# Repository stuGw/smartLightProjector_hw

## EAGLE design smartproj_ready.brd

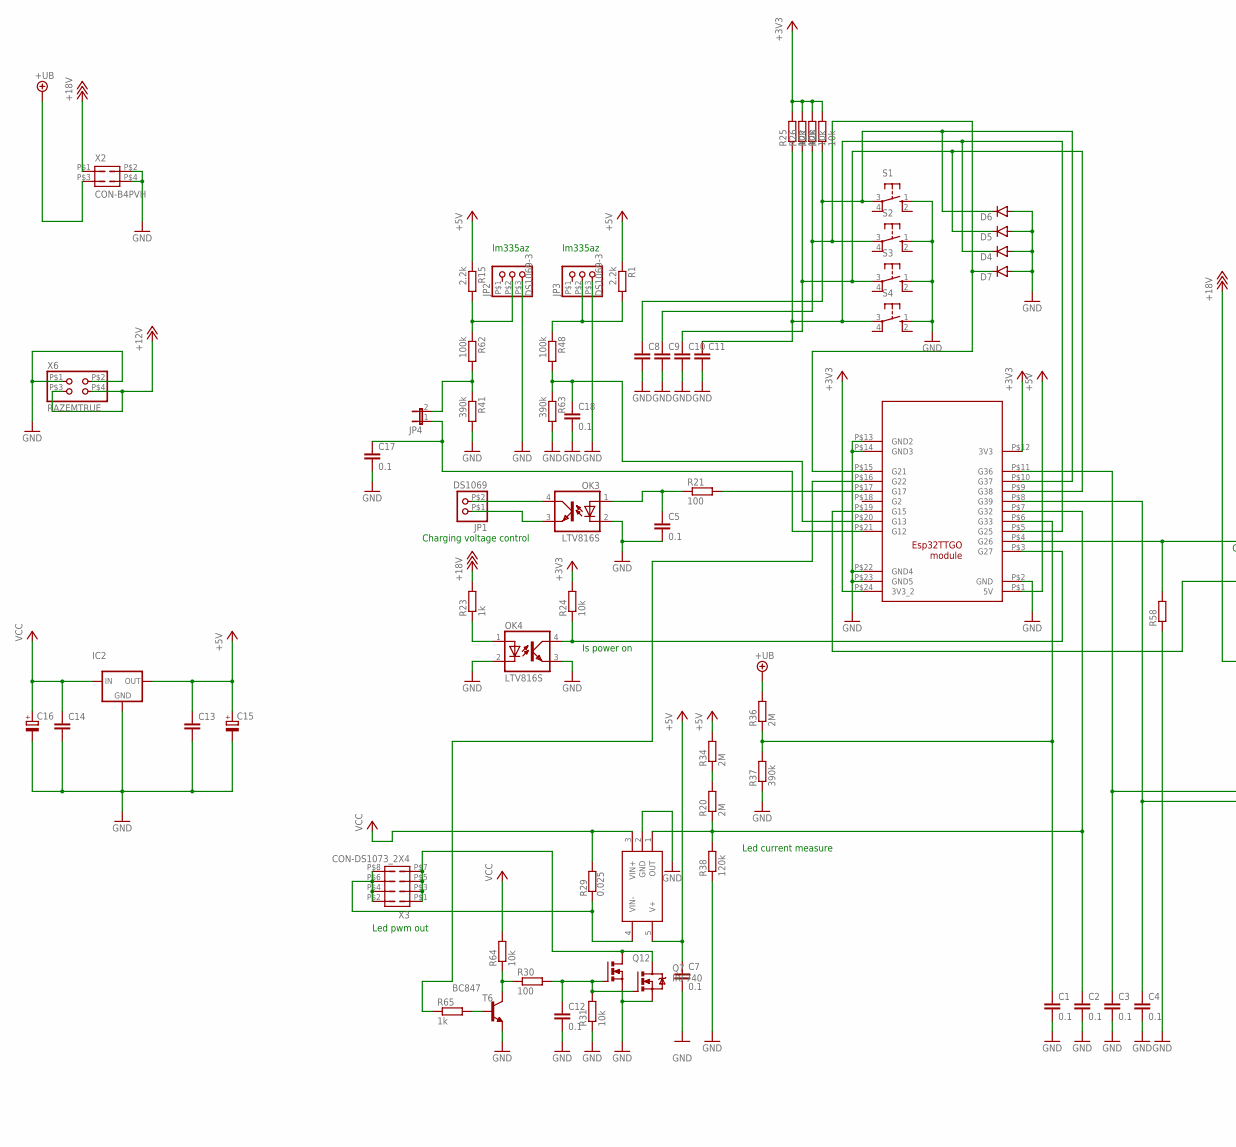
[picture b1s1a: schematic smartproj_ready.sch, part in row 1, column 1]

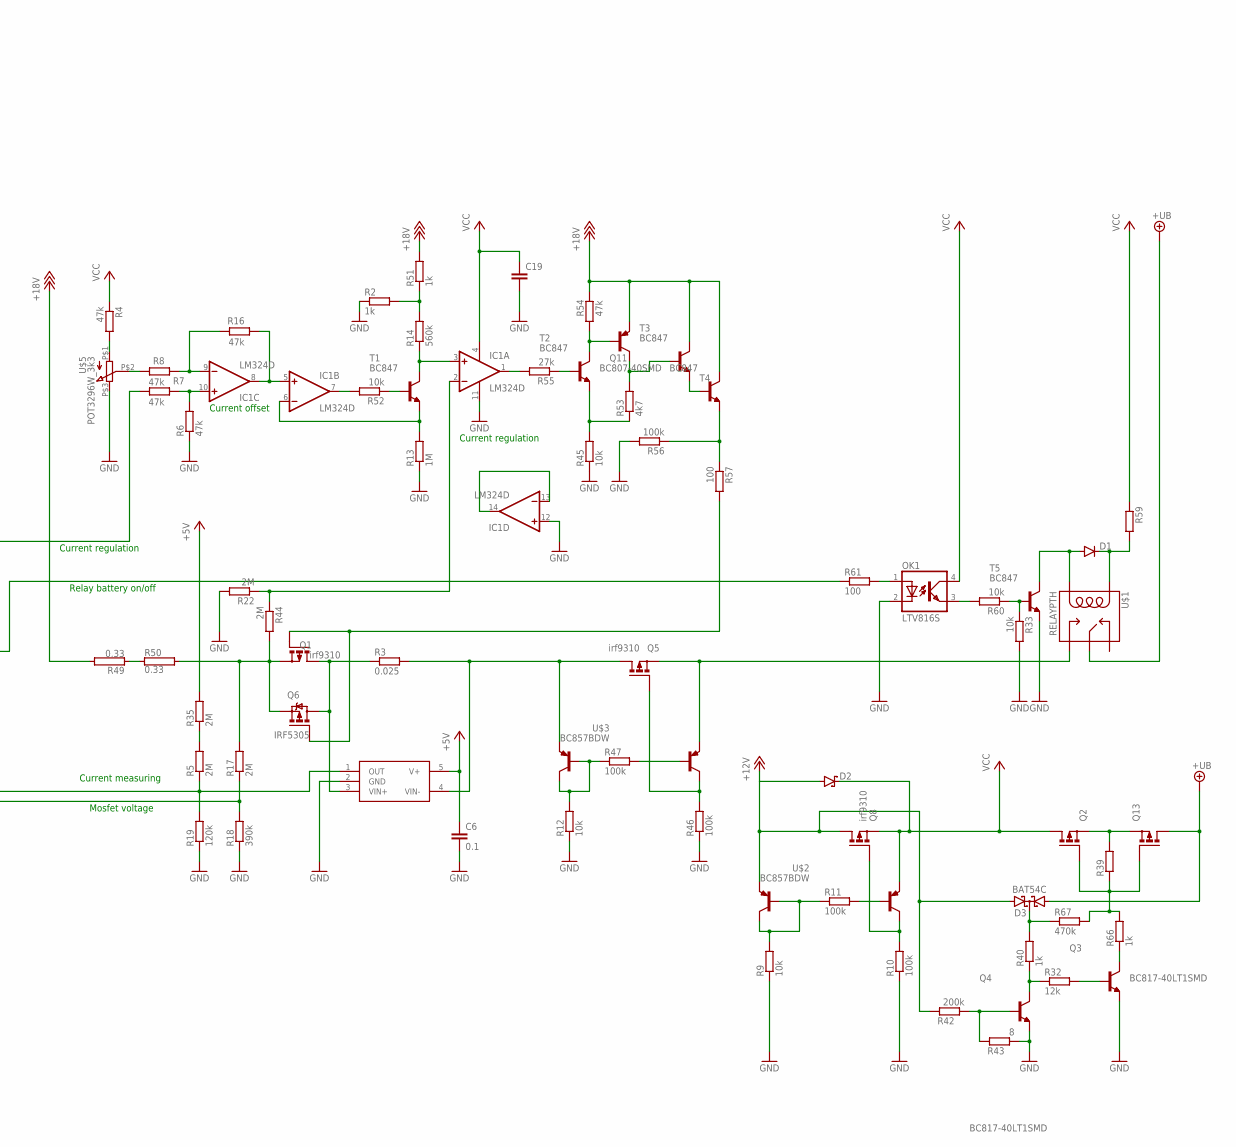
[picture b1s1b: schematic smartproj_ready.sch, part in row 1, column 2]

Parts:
C1, C2, C3, C4, C5, C6, C7, C12, C17, C18: 0.1; C0603K
C8, C9, C10, C11, C19: C-EUC0603K; C0603K
C13, C14: C-EUC0603; C0603
C15, C16: CPOL-EUSMCE; SMC_E
D1: DIODE-DO214AC; DO214AC
D2: SCHOTTKY-DIODESMC; SMC
D3: BAT54C; SOT23
D4, D5, D6, D7: DIODE-SOD323-W; SOD323-W
IC1: LM324D; SO14
IC2: 78XXS
JP1: DS1069; DS1069-2
JP2, JP3: DS1069-3
JP4: JP1E; JP1
OK1, OK3, OK4: LTV816S; DIL4-SMD
Q1, Q5, Q8: irf9310; SO-08
Q2, Q13: P-MOSFET-SO8; SO-08
Q3, Q4: BC817-40LT1SMD; SOT23-BEC
Q6: IRF5305; TO220BV
Q7: IRF740; TO220BV
Q11: BC807-40SMD; SOT23-BEC
Q12: N-MOSFET-SO8S; SO-08
R1, R15: 2.2k; R0603
R2, R23, R40, R51, R65, R66: 1k; R0603
R3, R29: 0.025; R2512
R4, R6, R7, R8, R16, R54: 47k; R0603
R5, R17, R20, R22, R34, R35, R36, R44: 2M; R0603
R9, R12, R24, R25, R26, R27, R28, R31, R33, R45, R52, R60, R64: 10k; R0603
R10, R11, R46, R47, R48, R56, R62: 100k; R0603
R13: 1M; R0603
R14: 560k; R0603
R18, R37, R41, R63: 390k; R0603
R19, R38: 120k; R0603
R21, R30, R57, R61: 100; R0603
R32: 12k; R0603
R39, R58: R-EU_R0603; R0603
R42: 200k; R0603
R43: 8; R0603
R49, R50: 0.33; CA4220
R53: 4k7; R0603
R55: 27k; R0603
R59: R-EU_R1206; R1206
R67: 470k; R0603
S1, S2, S3, S4: 10-XX; B3F-10XX
T1, T2, T3, T4, T5, T6: BC847; SOT23
U1: ESP32TTGO; ESP32TTGODIP
U3, U4: INA138; SOT23-DBV
U$1: RELAYPTH; SRD-05VDC-SL-C
U$2, U$3: BC857BDW; SOT363-INFINION
U$5: POT3296W_3k3; 3296W
X2: CON-B4PVH; B4PVH4
X3: CON-DS1073_2X4; DS1073_2X4
X6: RAZEMTRUE; DS1073_2X2N2

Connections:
+3V3: R24.2, R25.2, R26.2, R27.2, R28.2, U1.P$12 (3V3), U1.P$24 (3V3_2)
+5V: C6.1, C7.1, C13.1, C15.+, IC2.OUT, R1.1, R15.1, R34.2, R35.2, U1.P$1 (5V), U3.5 (V+), U4.5 (V+)
+12V: D2.A, D3.2 (A2), Q8.5 (D), Q8.6 (D), Q8.7 (D), Q8.8 (D), R42.2, U$2.1 (E1), X6.P$3 (3), X6.P$4 (4)
+18V: Q11.E, R23.2, R49.2, R51.2, R54.2, T3.3 (C), T4.3 (C), X2.P$1 (1)
+UB: D3.1 (A1), Q13.5 (D), Q13.6 (D), Q13.7 (D), Q13.8 (D), R36.2, U$1.SWCOMMON, X2.P$3 (3)
GND: C1.2, C2.2, C3.2, C4.2, C5.2, C6.2, C7.2, C8.2, C9.2, C10.2, C11.2, C12.2, C13.2, C14.2, C15.-, C16.-, C17.2, C18.2, C19.2, D4.A, D5.A, D6.A, D7.A, IC1.11 (V-), IC1.12 (+IN), IC2.GND, JP2.P$3 (3), JP3.P$3 (3), OK1.2 (C), OK3.2 (C), OK4.2 (C), OK4.3 (EMIT), Q3.E, Q4.E, Q7.S, Q12.1 (S), Q12.2 (S), Q12.3 (S), R2.1, R6.1, R9.1, R10.1, R12.1, R13.1, R18.1, R19.1, R22.2, R31.1, R33.2, R37.1, R38.1, R41.2, R43.1, R45.1, R46.1, R56.2, R58.1, R63.2, S1.1 (S), S2.1 (S), S3.1 (S), S4.1 (S), T5.2 (E), T6.2 (E), U1.P$2 (GND), U1.P$13 (GND2), U1.P$14 (GND3), U1.P$22 (GND4), U1.P$23 (GND5), U3.2 (GND), U4.2 (GND), U$5.P$3 (E), X2.P$2 (2), X2.P$4 (4), X6.P$1 (1), X6.P$2 (2)
unnamed: R49.1, R50.1
unnamed: OK1.3 (EMIT), R60.2
unnamed: Q4.B, R42.1, R43.2
unnamed: Q4.C, R32.1, R40.1
unnamed: Q3.B, R32.2
unnamed: Q2.4 (G), Q13.4 (G), R39.1, R66.2, R67.2
unnamed: Q1.1 (S), Q1.2 (S), Q1.3 (S), Q6.S, R17.2, R44.2, R50.2
unnamed: D3.3 (CC), R40.2, R67.1
unnamed: Q1.5 (D), Q1.6 (D), Q1.7 (D), Q1.8 (D), Q6.D, R3.1, U3.3 (VIN+)
unnamed: R4.2, U$5.P$1 (A)
unnamed: IC1.10 (+IN), R6.2, R7.1
unnamed: IC1.9 (-IN), R8.1, R16.2
unnamed: C1.1, R36.1, R37.2, U1.P$6 (G33)
unnamed: R11.2, U$2.5 (B)
unnamed: R52.1, T1.1 (B)
unnamed: IC1.13 (-IN), IC1.14 (OUT)
unnamed: R9.2, R11.1, U$2.2 (B1), U$2.6 (C1)
unnamed: Q8.4 (G), R10.2, U$2.3 (C)
unnamed: IC1.3 (+IN), R14.1, T1.3 (C)
unnamed: Q5.4 (G), R46.2, U$3.3 (C)
unnamed: IC1.6 (-IN), R13.2, T1.2 (E)
unnamed: IC1.1 (OUT), R55.2
unnamed: R8.2, U$5.P$2 (S)
unnamed: R20.2, R34.1
unnamed: IC1.5 (+IN), IC1.8 (OUT), R16.1
unnamed: C5.1, OK3.1 (A), R21.1
unnamed: JP1.P$2 (2), OK3.4 (COL)
unnamed: JP1.P$1 (1), OK3.3 (EMIT)
unnamed: OK4.1 (A), R23.1
unnamed: IC1.2 (-IN), R22.1, R44.1
unnamed: R5.2, R35.1
unnamed: R55.1, T2.1 (B)
unnamed: OK4.4 (COL), R24.1, U1.P$3 (G27)
unnamed: R12.2, R47.1, U$3.2 (B1), U$3.6 (C1)
unnamed: R30.1, R64.1, T6.3 (C)
unnamed: IC1.7 (OUT), R52.2
unnamed: C11.1, D4.C, R25.1, S4.3, U1.P$5 (G25)
unnamed: C10.1, D5.C, R26.1, S3.3, U1.P$9 (G38)
unnamed: R2.2, R14.2, R51.1
unnamed: R47.2, U$3.5 (B)
unnamed: R45.2, R53.1, T2.2 (E)
unnamed: Q2.1 (S), Q2.2 (S), Q2.3 (S), Q13.1 (S), Q13.2 (S), Q13.3 (S), R39.2
unnamed: Q5.1 (S), Q5.2 (S), Q5.3 (S), U$1.SWOPEN, U$3.4 (E)
unnamed: Q7.D, Q12.5 (D), Q12.6 (D), Q12.7 (D), Q12.8 (D), X3.P$1 (1), X3.P$3 (3), X3.P$5 (5), X3.P$7 (7)
unnamed: R21.2, U1.P$17 (G17)
unnamed: R65.1, U1.P$16 (G22)
unnamed: R7.2, R58.2, U1.P$4 (G26)
unnamed: C3.1, R5.1, R19.2, U1.P$11 (G36), U3.1 (OUT)
unnamed: Q11.C, R53.2, T3.1 (B)
unnamed: C17.1, JP4.1, U1.P$21 (G12)
unnamed: C4.1, R17.1, R18.2, U1.P$8 (G39)
unnamed: Q5.5 (D), Q5.6 (D), Q5.7 (D), Q5.8 (D), R3.2, U3.4 (VIN-), U$3.1 (E1)
unnamed: JP3.P$2 (2), R1.2, R48.1
unnamed: Q11.B, R54.1, T2.3 (C)
unnamed: C2.1, R20.1, R38.2, U1.P$7 (G32), U4.1 (OUT)
unnamed: JP2.P$2 (2), R15.2, R62.1
unnamed: C12.1, Q7.G, Q12.4 (G), R30.2, R31.2
unnamed: R65.2, T6.1 (B)
unnamed: JP4.2, R41.1, R62.2
unnamed: Q3.C, R66.1
unnamed: C18.1, R48.2, R63.1, U1.P$20 (G13)
unnamed: C8.1, D6.C, R28.1, S1.3, U1.P$10 (G37)
unnamed: C9.1, D7.C, R27.1, S2.3, U1.P$15 (G21)
unnamed: R56.1, R57.1, T4.2 (E)
unnamed: D1.A, T5.3 (C), U$1.COIL0
unnamed: T3.2 (E), T4.1 (B)
unnamed: Q1.4 (G), Q6.G, R57.2
unnamed: D1.C, R59.2, U$1.COIL1
unnamed: R33.1, R60.1, T5.1 (B)
unnamed: R61.1, U1.P$19 (G15)
unnamed: OK1.1 (A), R61.2
unnamed: R29.1, U4.4 (VIN-), X3.P$2 (2), X3.P$4 (4), X3.P$6 (6), X3.P$8 (8)
VCC: C14.1, C16.+, C19.1, D2.C, IC1.4 (V+), IC2.IN, OK1.4 (COL), Q2.5 (D), Q2.6 (D), Q2.7 (D), Q2.8 (D), Q8.1 (S), Q8.2 (S), Q8.3 (S), R4.1, R29.2, R59.1, R64.2, U4.3 (VIN+), U$2.4 (E)

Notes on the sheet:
lm335az
Charging voltage control
Is power on
Led pwm out
Led current measure
Current regulation
Current offset
Current measuring
Mosfet voltage
Relay battery on/off

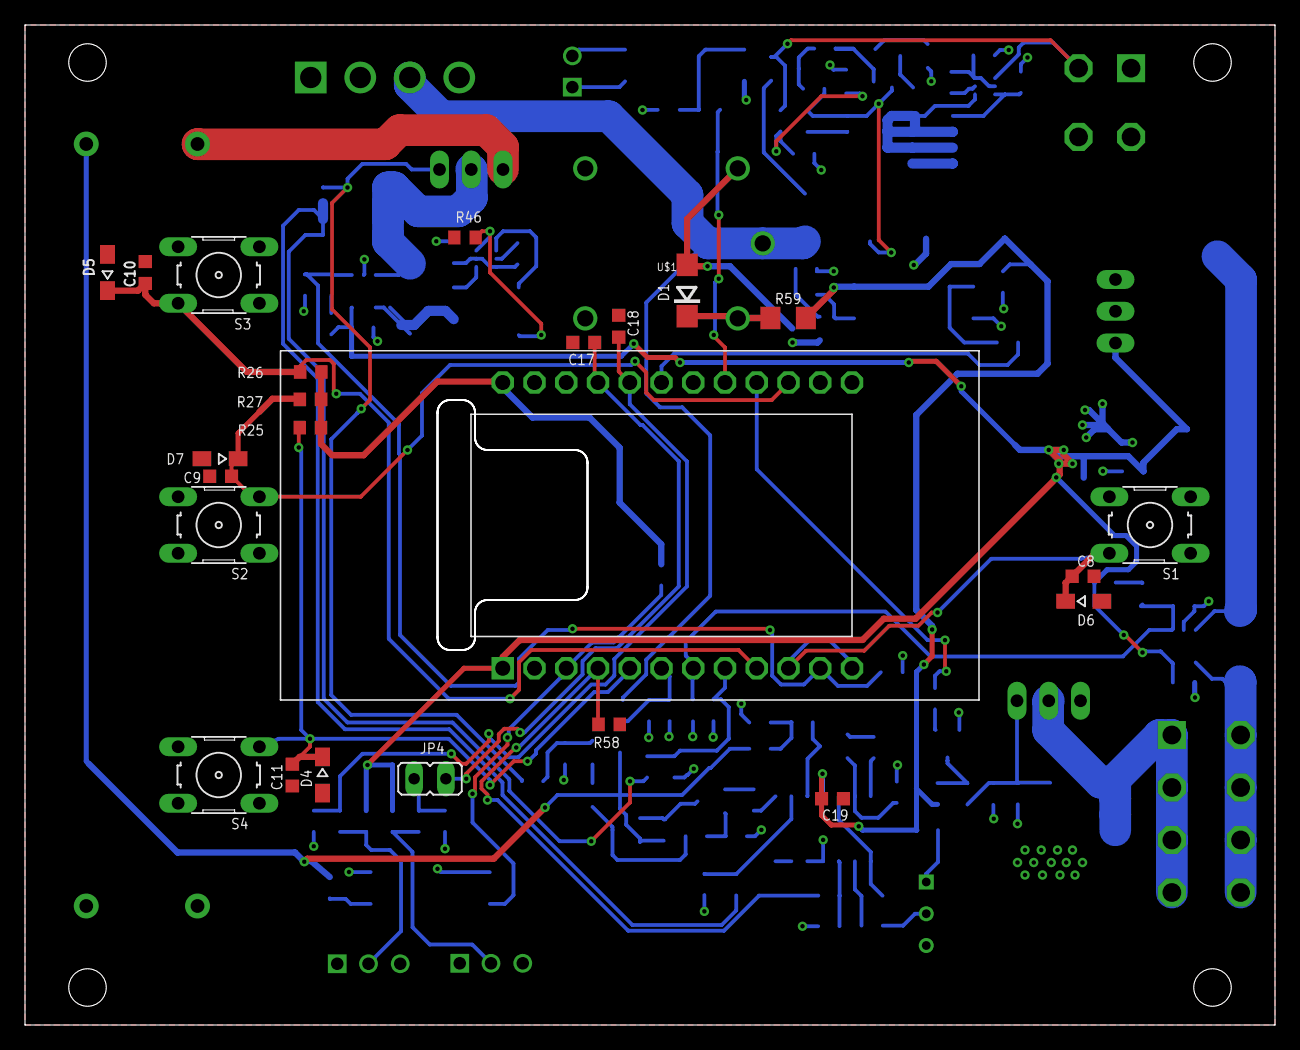
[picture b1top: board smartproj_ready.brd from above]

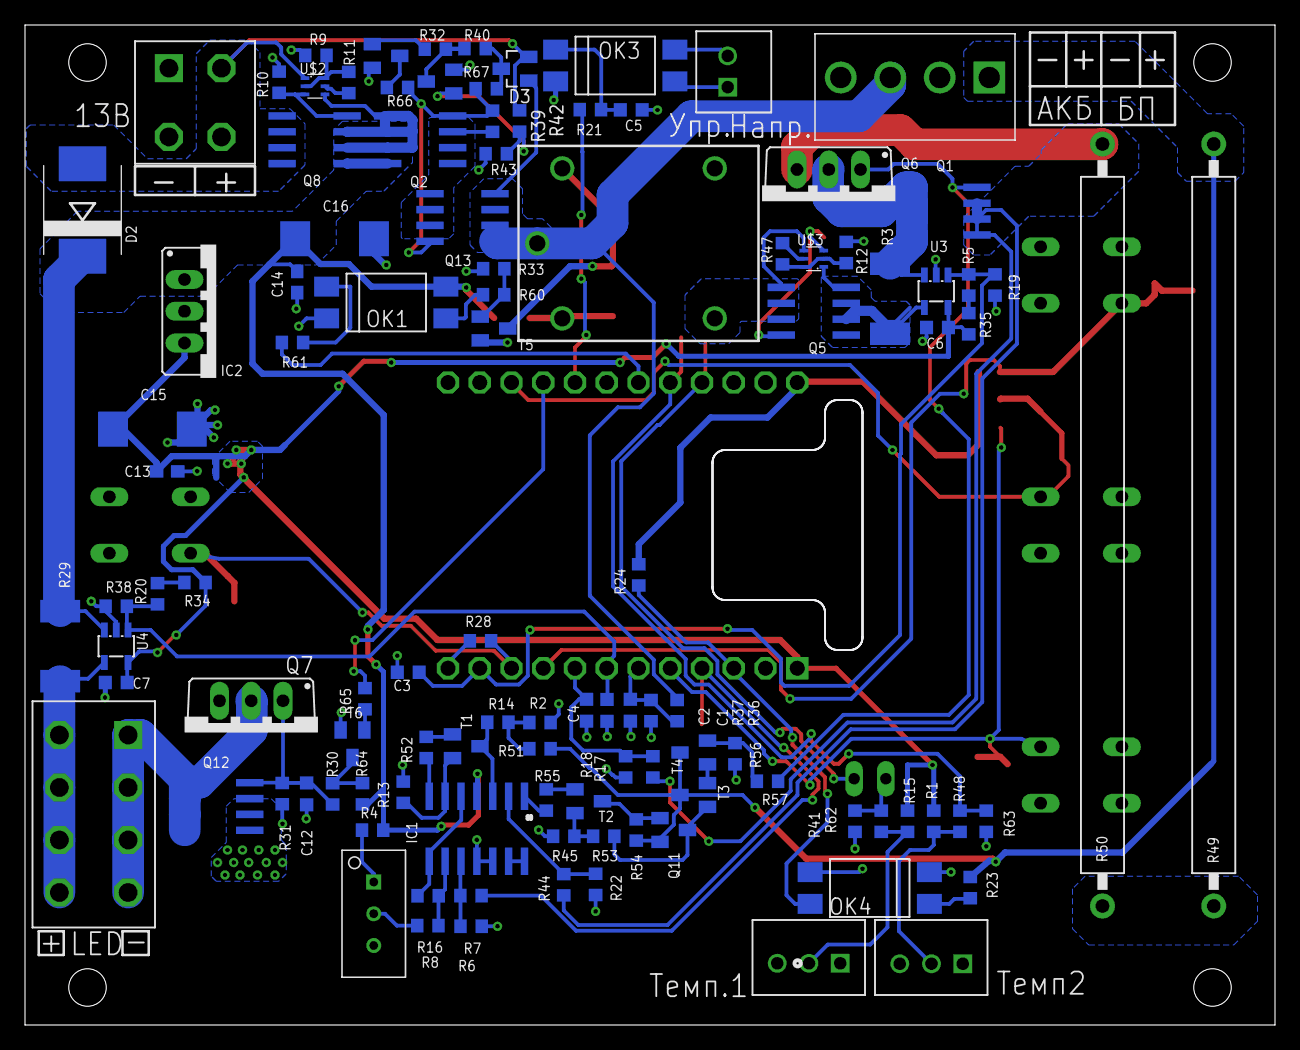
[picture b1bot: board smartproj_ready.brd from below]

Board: 2 copper layers, 99.8 x 79.8 mm, 133 parts (108 on the bottom side), 79 nets.

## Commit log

2022-05-18 release project v1.0
    e for your changes. Lines starting
